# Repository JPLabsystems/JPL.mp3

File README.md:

# JPL.mp3
*The iPod endgame does not exist.*  
An iPod-esque mp3 player based on the ESP32 platform.

See YouTube video and Blog post for more details!

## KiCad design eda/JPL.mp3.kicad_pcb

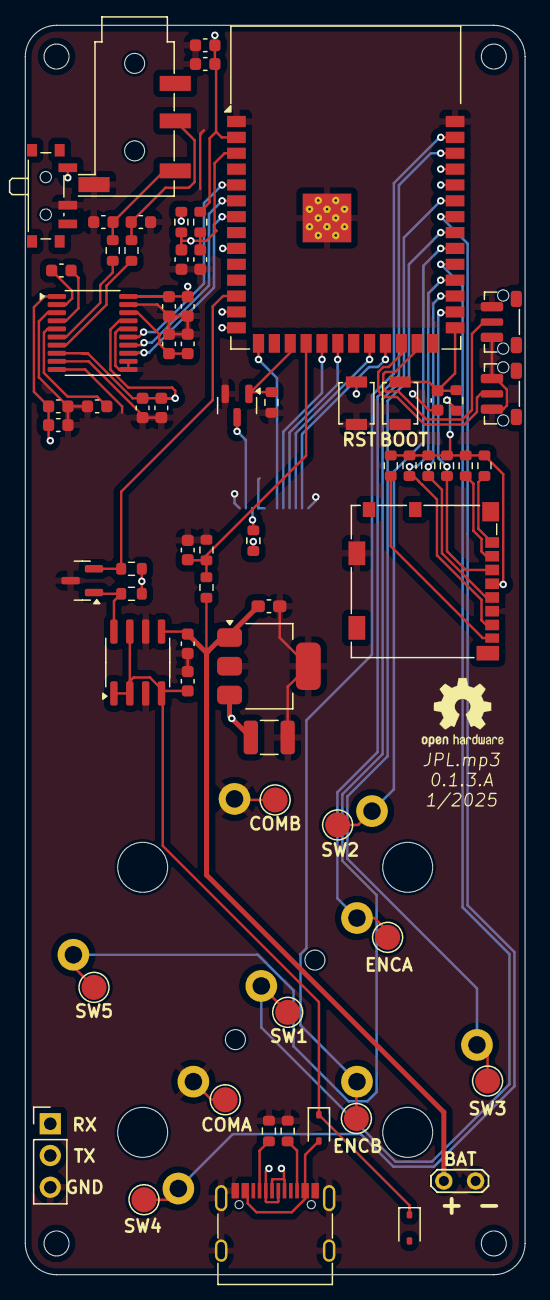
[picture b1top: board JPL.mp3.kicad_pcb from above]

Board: 4 copper layers, 40.0 x 100.0 mm, 70 parts (1 on the bottom side), 51 nets.

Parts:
BAT: TestPoint_2Pads_Pitch2.54mm_Drill0.8mm
BOOT1: BOOT; SW_SPST_B3U-1000P
C1: .47uF; C_0603_1608Metric_Pad1.08x0.95mm_HandSolder
C2: 47uF; C_1210_3225Metric
C3, C4: 2.2nF; C_0603_1608Metric
C5, C9, C15, C19, C21: .1uF; C_0603_1608Metric
C6, C10, C16, C20, C23: 10uF; C_0603_1608Metric
C7: 2.2 uF; C_0603_1608Metric
C8: 10 nF; C_0603_1608Metric
C11, C13: 0.1uF; C_0603_1608Metric
C12: 1uF; C_0603_1608Metric
C14: 4.7 uF; C_0603_1608Metric
C17, C18: 2.2uF; C_0603_1608Metric
COMA: TestPoint_Pad_D2.0mm
COMB: TestPoint_Pad_D2.0mm
D1, D2: 1N5819WS; D_SOD-323
ENCA: TestPoint_Pad_D2.0mm
ENCB: TestPoint_Pad_D2.0mm
Enc1: ANO Rotary Encoder
J1: Micro_SD_Card; microSD_HC_Molex_104031-0811
J2: USB_C; USB_C_Receptacle_G-Switch_GT-USB-7010ASV
J4: Conn_01x12; TE_1-1734839-2_1x12-1MP_P0.5mm_Horizontal
J5: AudioJack3; Jack_3.5mm_KoreanHropartsElec_PJ-320D-4A_Horizontal
J6: Conn_01x03_Pin; PinHeader_1x03_P2.54mm_Vertical
Q1, Q2: BSS138; SOT-23
R1, R2: 5.1K; R_0603_1608Metric
R3, R8, R9, R10, R11, R13, R14, R15, R16, R17, R18, R19: 10K; R_0603_1608Metric
R4, R5: 470; R_0603_1608Metric
R6, R7: 100K; R_0603_1608Metric
R12: 10; R_0603_1608Metric
RST1: SW_SPST; SW_SPST_B3U-1000P
SL2: HOLD; SW_SPDT_PCM12
SW1, SW2#2, SW3, SW4, SW5: TestPoint_Pad_D2.0mm
SW1#2, SW2: SW_Push; SW_Push_1P1T-MP_NO_Horizontal_Alps_SKRTLAE010
U1: ESP32-S3-WROOM-1
U2: MAX1811; SOIC-8_3.9x4.9mm_P1.27mm
U4: PCM5102A; TSSOP-20_4.4x6.5mm_P0.65mm
U5: LT1963AxST-3.3; SOT-223-3_TabPin2

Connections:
+3.3V: C2.1, C6.1, C9.1, C10.1, C15.1, C19.2, C20.1, C21.2, C23.1, J1.4 (VDD), J4.8, J4.9, R3.1, R8.2, R9.1, R10.2, R12.1, R13.2, R14.1, R15.2, R16.2, R17.1, R18.1, R19.1, U1.2 (3V3), U4.1 (CPVDD), U4.8 (AVDD), U4.17 (XSMT), U4.20 (DVDD), U5.3 (OUT)
+5V: C14.1, D1.1 (K), D2.1 (K), U2.1 (SELV), U2.2 (SELI), U2.4 (IN), U2.7 (EN)
AUDIO_LEFT: C3.1, J5.T, R4.2
AUDIO_RIGHT: C4.1, J5.R1, R5.2
BACKLIGHT: Q2.1 (G), R11.1, U1.17 (GPIO9/TOUCH9/ADC1_CH8/FSPIHD/SUBSPIHD)
BAT_SENSE: C8.2, R6.2, R7.1, U1.18 (GPIO10/TOUCH10/ADC1_CH9/FSPICS0/FSPIIO4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)
CHG: Q1.2 (S), R10.1, U1.12 (GPIO8/TOUCH8/ADC1_CH7/SUBSPICS1)
ENCA: Enc1.A, U1.38 (GPIO2/TOUCH2/ADC1_CH1)
ENCB: Enc1.B, U1.39 (GPIO1/TOUCH1/ADC1_CH0)
GND: BAT.2, BOOT1.2 (B), C1.2, C2.2, C3.2, C4.2, C5.1, C6.2, C7.2, C8.1, C9.2, C10.2, C11.2, C12.2, C13.2, C14.2, C15.2, C16.1, C18.2, C19.1, C20.2, C21.1, C23.2, Enc1.COM_A, Enc1.COM_B, J1.6 (VSS), J1.11, J2.A1 (GND), J2.A12 (GND), J2.B1 (GND), J2.B12 (GND), J2.S1 (SHIELD), J4.1, J4.12, J5.S, J6.3, Q1.3 (D), Q2.2 (S), R1.2, R2.2, R7.2, R11.2, RST1.1 (A), SL2.2 (B), SW1#2.1, SW2.1, U1.1 (GND), U1.40 (GND), U1.41 (GND), U2.3 (GND), U2.6 (GND), U4.3 (CPGND), U4.9 (AGND), U4.10 (DEMP), U4.11 (FLT), U4.12 (SCK), U4.16 (FMT), U4.19 (DGND), U5.2 (GND)
HOLD: SL2.1 (A), U1.9 (GPIO16/U0CTS/ADC2_CH5/XTAL_32K_N)
I2S_LRCLK: U1.5 (GPIO5/TOUCH5/ADC1_CH4), U4.15 (LRCK)
I2S_SCLK: U1.7 (GPIO7/TOUCH7/ADC1_CH6), U4.13 (BCK)
I2S_SD: U1.6 (GPIO6/TOUCH6/ADC1_CH5), U4.14 (DIN)
unnamed: BOOT1.1 (A), C11.1, R17.2, U1.27 (GPIO0/BOOT)
unnamed: C1.1, C7.1, R6.1, U2.5 (BATT), U5.1 (IN)
unnamed: D1.2 (A), J2.A4 (VBUS), J2.A9 (VBUS), J2.B4 (VBUS), J2.B9 (VBUS)
unnamed: J1.8 (DAT1), R8.1
unnamed: J1.1 (DAT2), R9.2
unnamed: J1.2 (DAT3/CD), R3.2
unnamed: J2.A5 (CC1), R1.1
unnamed: J2.B5 (CC2), R2.1
unnamed: J4.10, R12.2
unnamed: J4.11, Q2.3 (D)
unnamed: Q1.1 (G), R13.1, U2.8 (~CHG)
unnamed: C12.1, C13.1, R18.2, R19.2, RST1.2 (B), U1.3 (EN)
unnamed: C17.2, U4.4 (CAPM)
unnamed: C17.1, U4.2 (CAPP)
unnamed: C5.2, C16.2, U4.18 (LDOO)
unnamed: R4.1, U4.6 (OUTL)
unnamed: R5.1, U4.7 (OUTR)
unnamed: C18.1, U4.5 (VNEG)
SD_CLK: J1.5 (CLK), R16.1, U1.29 (SPIIO7/GPIO36/FSPICLK/SUBSPICLK)
SD_CMD: J1.3 (CMD), R14.2, U1.28 (SPIIO6/GPIO35/FSPID/SUBSPID)
SD_D0: J1.7 (DAT0), R15.1, U1.30 (SPIDQS/GPIO37/FSPIQ/SUBSPIQ)
SW1: Enc1.S1, U1.31 (GPIO38/FSPIWP/SUBSPIWP)
SW2: Enc1.S2, U1.32 (MTCK/GPIO39/CLK_OUT3/SUBSPICS1)
SW3: Enc1.S3, U1.33 (MTDO/GPIO40/CLK_OUT2)
SW4: Enc1.S4, U1.34 (MTDI/GPIO41/CLK_OUT1)
SW5: Enc1.S5, U1.35 (MTMS/GPIO42)
TFT_CS: J4.2, U1.23 (GPIO21)
TFT_DC: J4.3, U1.22 (GPIO14/TOUCH14/ADC2_CH3/FSPIWP/FSPIDQS/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)
TFT_RST: J4.6, U1.15 (GPIO3/TOUCH3/ADC1_CH2)
TFT_SCLK: J4.4, U1.20 (GPIO12/TOUCH12/ADC2_CH1/FSPICLK/FSPIIO6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)
TFT_SDA: J4.5, U1.19 (GPIO11/TOUCH11/ADC2_CH0/FSPID/FSPIIO5/S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)
UART_RX: J6.1, U1.36 (U0RXD/GPIO44/CLK_OUT2)
UART_TX: J6.2, U1.37 (U0TXD/GPIO43/CLK_OUT1)
USB_D+: J2.A6 (D+), J2.B6 (D+), U1.14 (GPIO20/U1CTS/ADC2_CH9/CLK_OUT1/USB_D+)
USB_D-: J2.A7 (D-), J2.B7 (D-), U1.13 (GPIO19/U1RTS/ADC2_CH8/CLK_OUT2/USB_D-)
VOL_DOWN: SW2.2, U1.24 (GPIO47/SPICLK_P/SUBSPICLK_P_DIFF)
VOL_UP: SW1#2.2, U1.25 (GPIO48/SPICLK_N/SUBSPICLK_N_DIFF)

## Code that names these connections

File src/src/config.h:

#ifndef config_h
#define config_h

/////////PIN DEFINITIONS/////////

#define batSensePin 10
#define chargeSensePin 8

#define TFT_CS 21
#define TFT_RST 3
#define TFT_DC 14

// encoder pins
#define encA 1
#define encB 2

const int left = 40;
#define up 39
#define down 41
#define right 42
#define center 38
#define vUp 47
#define vDown 48
const int hold = 16;

// #define I2S_MCLK 3
#define I2S_DOUT 6
#define I2S_BCLK 7
#define I2S_LRC 5

#endif

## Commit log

2024-12-21 Create src
2025-01-02 Create eda
2025-07-11 test
2025-07-11 more cad
2025-07-11 readme
2025-07-11 formating
2025-07-11 more format
2025-07-11 still
2025-07-11 details
2025-07-11 forafsdkfjadkjsfhldsa
2025-07-12 mp script
2025-07-12 bleh
2025-08-03 files
2025-08-03 production files
2025-08-03 Fixed bom
2025-08-03 note
2025-09-06 Add files via upload
    Modified Backplate
